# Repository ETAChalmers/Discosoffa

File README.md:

# Discosoffa
Repo för allt vad gäller den fabulösa Discosoffan!

# Index
[Modular BMS](#Modular-BMS)

[MCU-kort](#MCU-kort)

# Modular BMS
Det BMS (Battery Management System) vilket används på soffan är Jonathan Locks egendesignade Modular BMS-projekt. 
PCB-design, kod samt dokumentation för dessa finns att tillgå från hans [GitLab repository](https://gitlab.com/lerneaen_hydra/rabidmantis/tree/master/modular_bms).

Discosoffans batteripack är på 5-celler seriellt (5S). För detta behövs en modul per cell, varav en är master.

Följande är de konfigurationer Discosoffans BMS-moduler använder. Dessa anges i _config.h_.
```c
/** @brief Voltage which gives 100%-active discharge output [volt]
 * Voltages above this value will also keep the discharge output fully on */
#define VTHRS_DISCH_MAX_V				4.00

/** @brief Voltage which gives 0%-active discharge output [volt]
 * Voltages below this value will also keep the discharge output fully off */
#define VTHRS_DISCH_MIN_V				3.95

/** @brief Threshold voltage for activating the charge-disable output [volt] */
#define VTHRS_CHGDIS_START_V			4.05

/** @brief Threshold voltage for de-activating the charge-disable output [volt] */
#define VTHRS_CHGDIS_STOP_V				4.00

/** @brief Threshold voltage for triggering an undervoltage alarm [volt]
 * See also TMIN_UV_ALARM_S */
#define VTHRS_UV_ALARM_V				3.50

/** @brief Threshold voltage for triggering an overvoltage alarm [volt] */
#define VTHRS_OV_ALARM_V				4.10

/** @brief Voltage hysteresis for leaving alarm state [volt]
 * To leave the undervoltage alarm the sampled voltage must exceed
 * VTHRS_UV_ALARM_V + VHYST_ALARMS_V, and to leave the overvoltage
 * alarm the sampled voltage must be below
 * VTHRS_OV_ALARM_V - VHYST_ALARMS_V */
#define VHYST_ALARMS_V					0.05

/** @brief Minimum time the charger will be kept disabled after voltage exceeds
* VTHRS_CHGDIS_START_mv [seconds] */
#define TMIN_CHGDIS_S					30.0

/** @brief Minimum time voltage must be below VTHRS_UV_ALARM_V to trigger an
 * alarm [seconds] */
#define TMIN_UV_ALARM_S					60.0
```

BMS-modulerna är monterade i 3D-printade hållare. 3D STEP-filerna till dessa finns i [bms_box](/mechanics/bms_box). Dessa ser ut som nedan:

# MCU-kort
Kortet vilket sköter styrningen av soffan. Denna huserar en Nucleo-F401RE dev board.

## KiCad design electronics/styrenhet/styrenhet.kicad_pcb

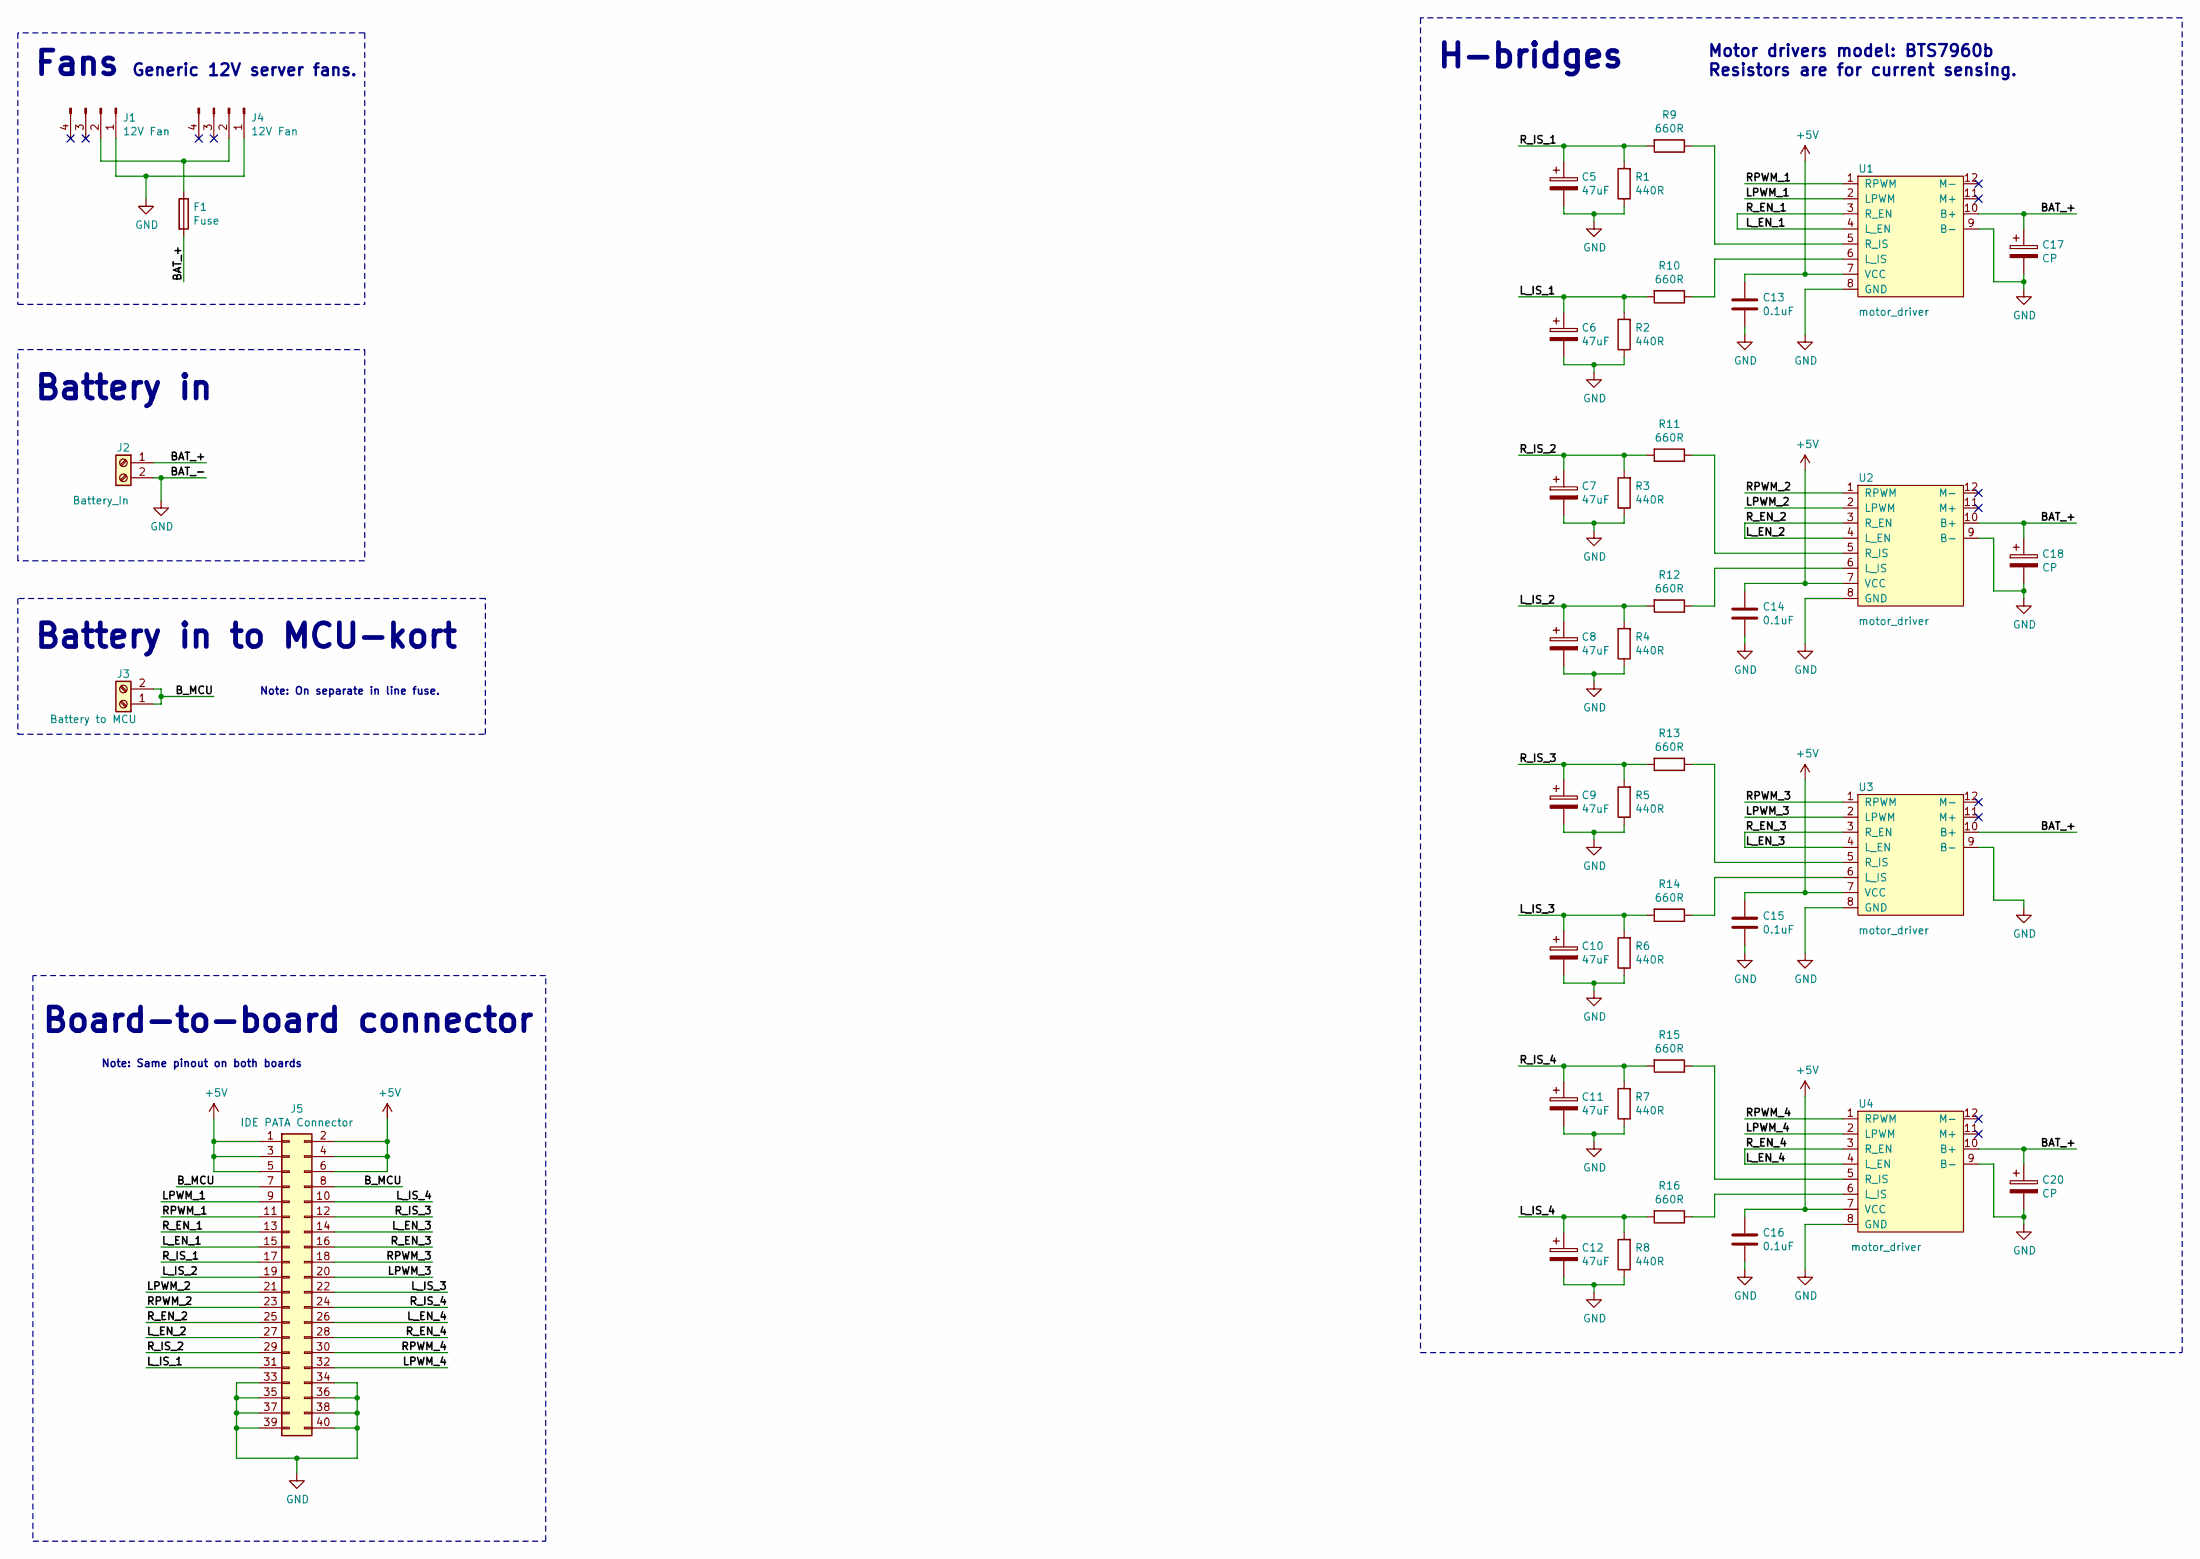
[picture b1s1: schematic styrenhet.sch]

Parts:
C5, C6, C7, C8, C9, C10, C11, C12: 47uF; CP_Radial_D10.0mm_P5.00mm
C13, C14, C15, C16: 0.1uF; C_0805_HandSoldering
C17, C18, C20: CP; CP_Radial_D22.0mm_P10.00mm_SnapIn
F1: Fuse; ETA_thl_fuseholder
J1, J4: 12V Fan; Pin_Header_Straight_1x04_Pitch2.54mm
J2: Battery_In; TerminalBlock-XXL
J3: Battery to MCU; TerminalBlock_Phoenix_MKDS1.5-2pol
J5: IDE PATA Connector; IDC-Header_2x20_Pitch2.54mm_Straight
R1, R2, R3, R4, R5, R6, R7, R8: 440R; R_0603_HandSoldering
R9, R10, R11, R12, R13, R14, R15, R16: 660R; R_0603_HandSoldering
U1, U2, U3, U4: motor_driver; motor-driver

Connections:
+5V: C13.1, C14.1, C15.1, C16.1, J5.1, J5.2, J5.3, J5.4, J5.5, J5.6, U1.7 (VCC), U2.7 (VCC), U3.7 (VCC), U4.7 (VCC)
/BAT_+: C17.1, C18.1, C20.1, F1.2, J2.1, U1.10 (B+), U2.10 (B+), U3.10 (B+), U4.10 (B+)
/B_MCU: J3.1, J3.2, J5.7, J5.8
/LPWM_1: J5.9, U1.2 (LPWM)
/LPWM_2: J5.21, U2.2 (LPWM)
/LPWM_3: J5.20, U3.2 (LPWM)
/LPWM_4: J5.32, U4.2 (LPWM)
/L_EN_1: J5.13, J5.15, U1.3 (R_EN), U1.4 (L_EN)
/L_EN_2: J5.25, J5.27, U2.3 (R_EN), U2.4 (L_EN)
/L_EN_3: J5.14, J5.16, U3.3 (R_EN), U3.4 (L_EN)
/L_EN_4: J5.26, J5.28, U4.3 (R_EN), U4.4 (L_EN)
/L_IS_1: C6.1, J5.31, R2.2, R10.2
/L_IS_2: C8.1, J5.19, R4.2, R12.2
/L_IS_3: C10.1, J5.22, R6.2, R14.2
/L_IS_4: C12.1, J5.10, R8.2, R16.2
/RPWM_1: J5.11, U1.1 (RPWM)
/RPWM_2: J5.23, U2.1 (RPWM)
/RPWM_3: J5.18, U3.1 (RPWM)
/RPWM_4: J5.30, U4.1 (RPWM)
/R_IS_1: C5.1, J5.17, R1.2, R9.2
/R_IS_2: C7.1, J5.29, R3.2, R11.2
/R_IS_3: C9.1, J5.12, R5.2, R13.2
/R_IS_4: C11.1, J5.24, R7.2, R15.2
GND: C5.2, C6.2, C7.2, C8.2, C9.2, C10.2, C11.2, C12.2, C13.2, C14.2, C15.2, C16.2, C17.2, C18.2, C20.2, J1.1, J2.2, J4.1, J5.33, J5.34, J5.35, J5.36, J5.37, J5.38, J5.39, J5.40, R1.1, R2.1, R3.1, R4.1, R5.1, R6.1, R7.1, R8.1, U1.8 (GND), U1.9 (B-), U2.8 (GND), U2.9 (B-), U3.8 (GND), U3.9 (B-), U4.8 (GND), U4.9 (B-)
unnamed: F1.1, J1.2, J4.2
unnamed: R9.1, U1.5 (R_IS)
unnamed: R10.1, U1.6 (L_IS)
unnamed: R11.1, U2.5 (R_IS)
unnamed: R12.1, U2.6 (L_IS)
unnamed: R13.1, U3.5 (R_IS)
unnamed: R14.1, U3.6 (L_IS)
unnamed: R15.1, U4.5 (R_IS)
unnamed: R16.1, U4.6 (L_IS)

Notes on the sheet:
Note: Same pinout on both boards
H-bridges
Motor drivers model: BTS7960b Resistors are for current sensing.
Board-to-board connector
Fans
Generic 12V server fans.
Battery in
Battery in to MCU-kort
Note: On separate in line fuse.

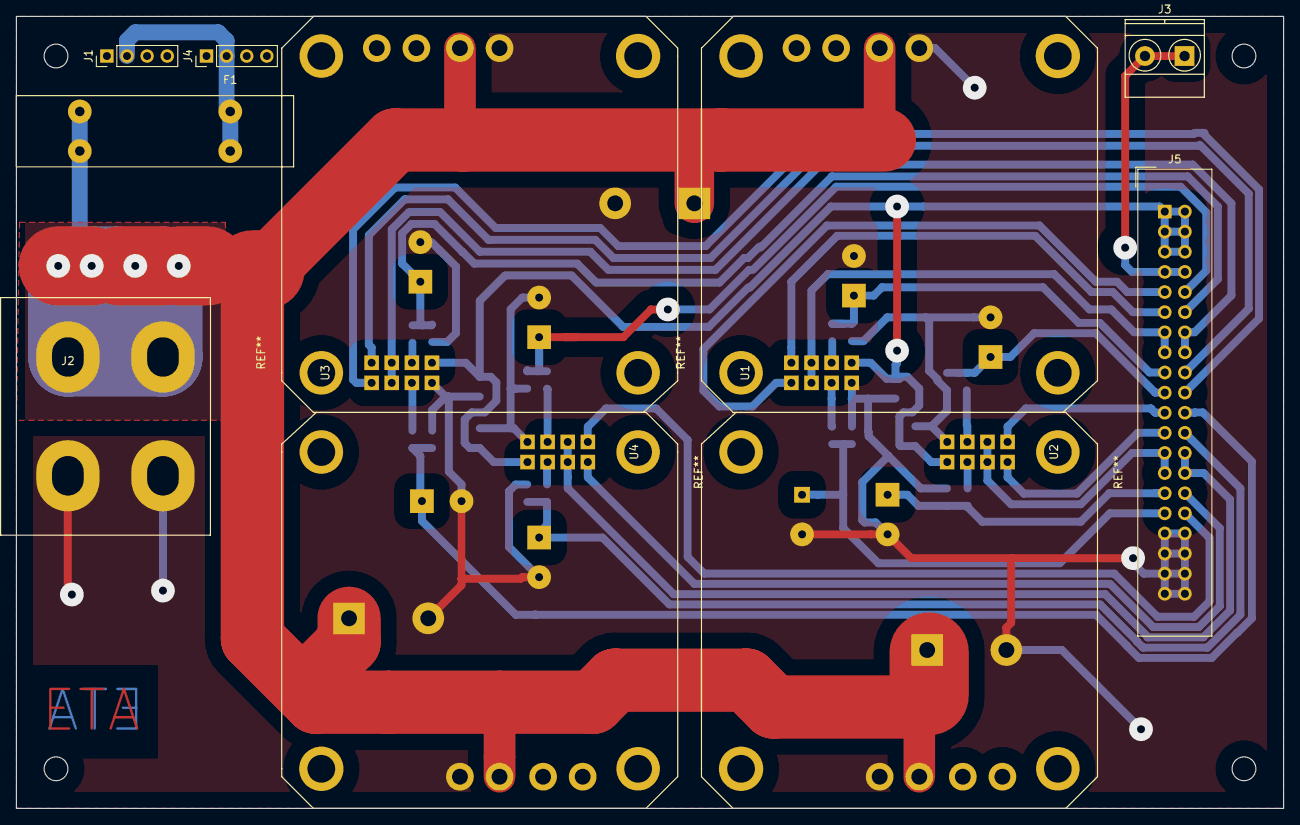
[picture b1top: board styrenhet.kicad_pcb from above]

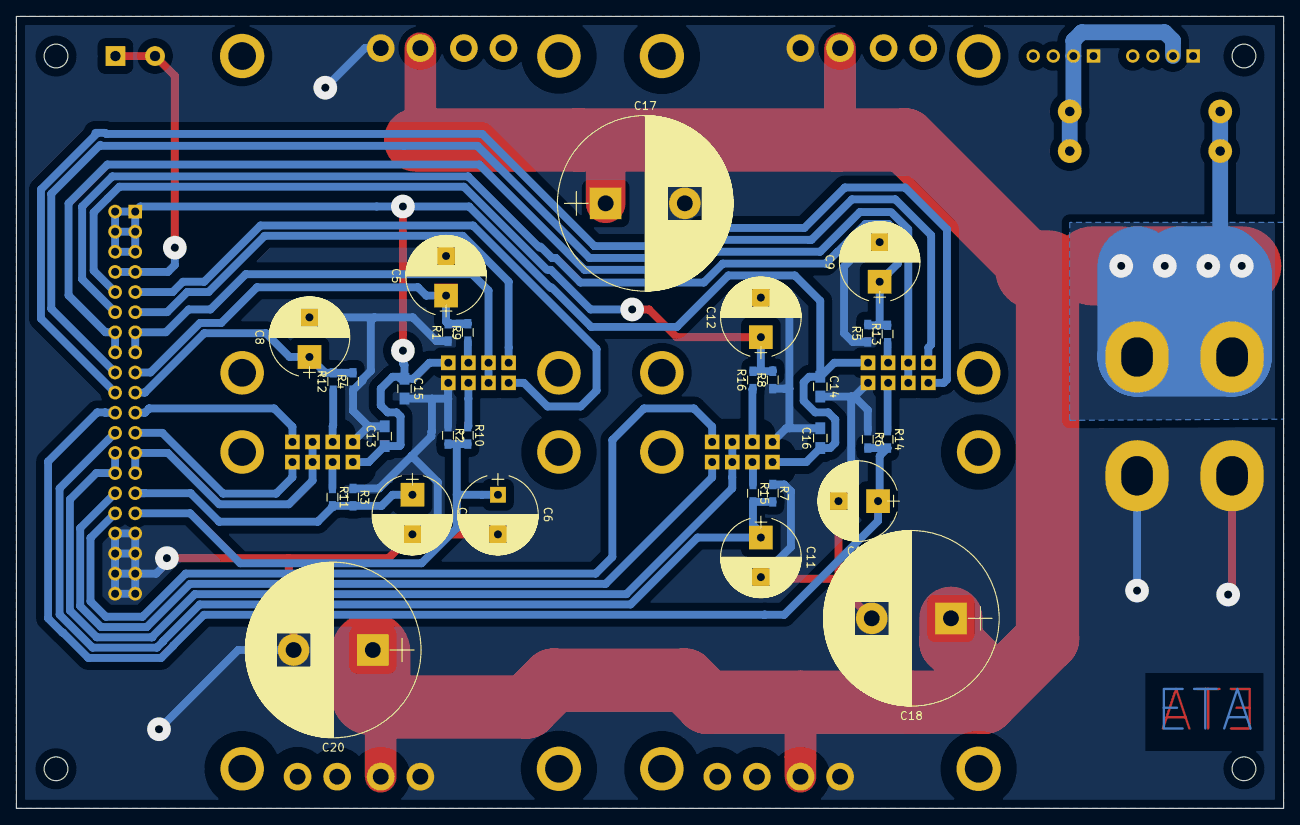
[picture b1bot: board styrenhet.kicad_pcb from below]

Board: 2 copper layers, 160.0 x 100.0 mm, 41 parts (31 on the bottom side), 33 nets.

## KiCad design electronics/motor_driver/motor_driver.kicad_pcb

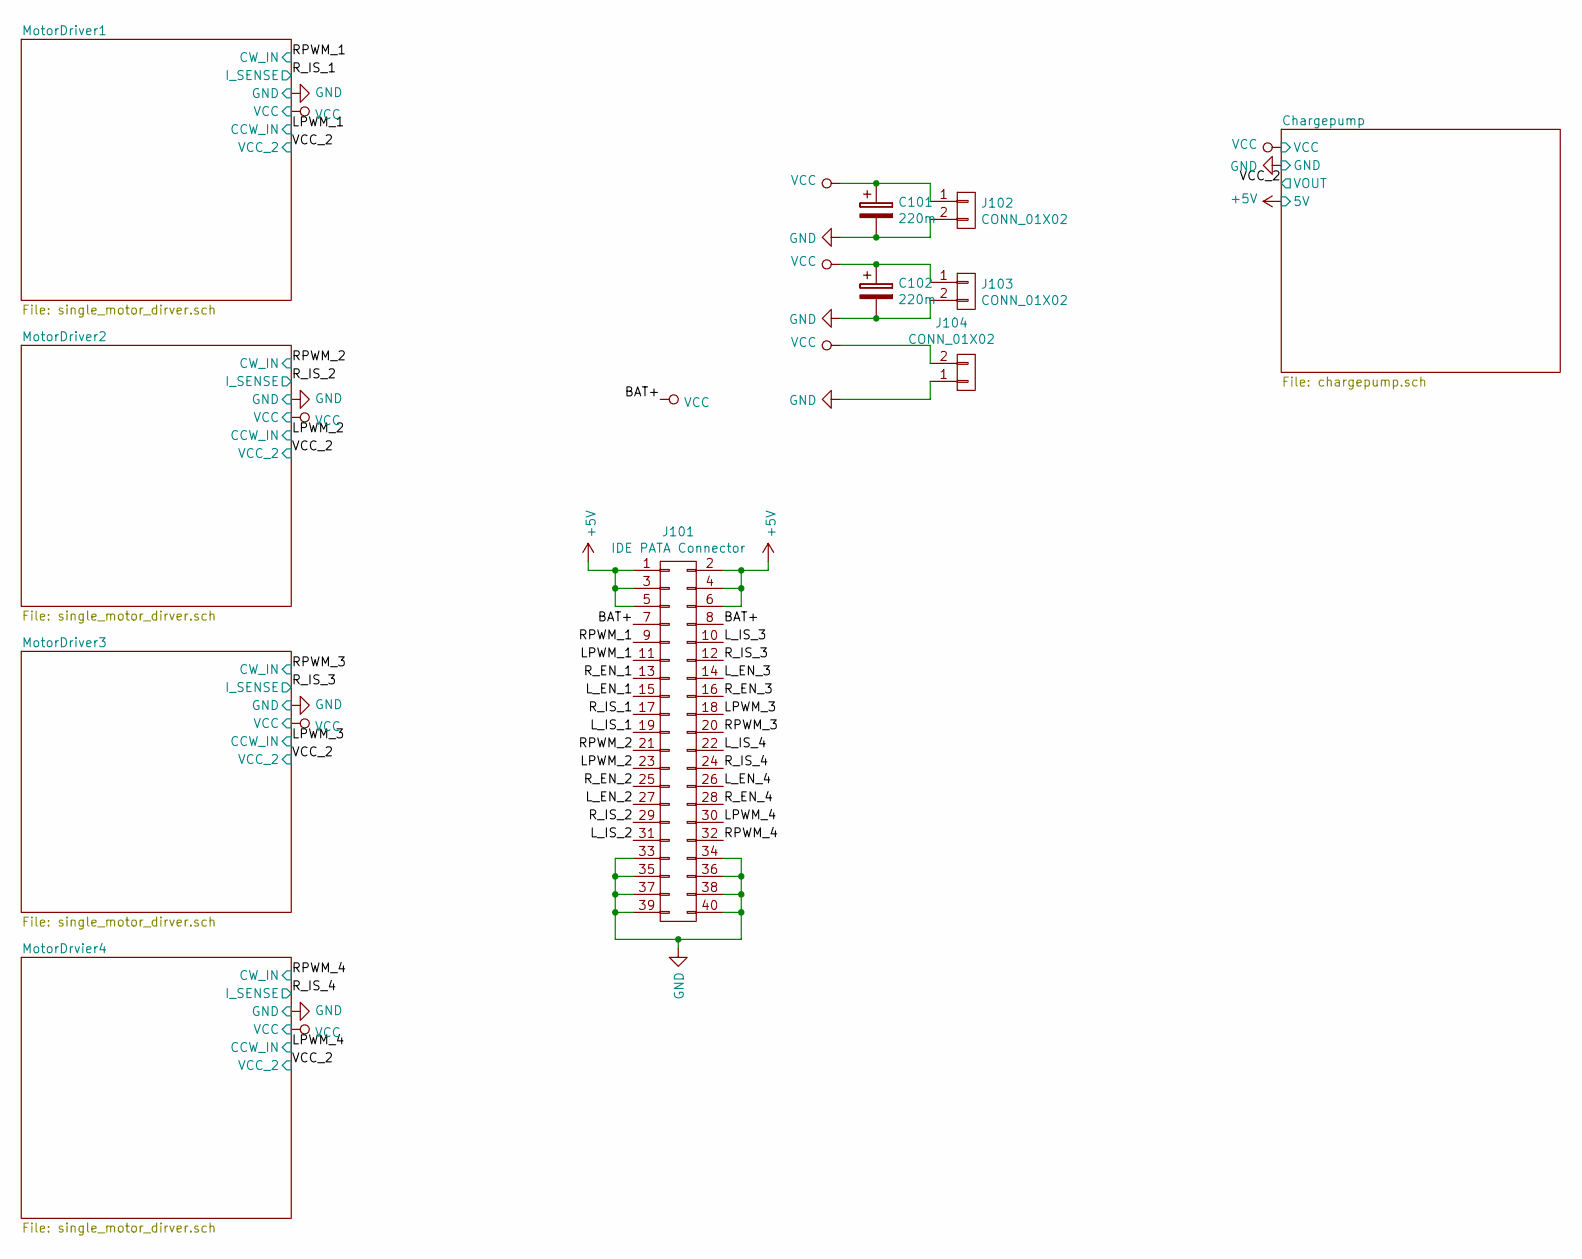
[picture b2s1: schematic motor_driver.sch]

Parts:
C101, C102: 220m; CP_Radial_D25.0mm_P10.00mm_SnapIn
J101: IDE PATA Connector; IDC-Header_2x20_Pitch2.54mm_Straight
J102, J103, J104: CONN_01X02; TerminalBlock-XXL

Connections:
+5V: J101.1, J101.2, J101.3, J101.4, J101.5, J101.6; also elsewhere on the board
/LPWM_1: J101.11; also elsewhere on the board
/LPWM_2: J101.23; also elsewhere on the board
/LPWM_3: J101.18; also elsewhere on the board
/LPWM_4: J101.30; also elsewhere on the board
/L_EN_1: J101.15
/L_EN_2: J101.27
/L_EN_3: J101.14
/L_EN_4: J101.26
/L_IS_1: J101.19
/L_IS_2: J101.31
/L_IS_3: J101.10
/L_IS_4: J101.22
/RPWM_1: J101.9; also elsewhere on the board
/RPWM_2: J101.21; also elsewhere on the board
/RPWM_3: J101.20; also elsewhere on the board
/RPWM_4: J101.32; also elsewhere on the board
/R_EN_1: J101.13
/R_EN_2: J101.25
/R_EN_3: J101.16
/R_EN_4: J101.28
/R_IS_1: J101.17; also elsewhere on the board
/R_IS_2: J101.29; also elsewhere on the board
/R_IS_3: J101.12; also elsewhere on the board
/R_IS_4: J101.24; also elsewhere on the board
GND: C101.2, C102.2, J101.33, J101.34, J101.35, J101.36, J101.37, J101.38, J101.39, J101.40, J102.2, J103.2, J104.1; also elsewhere on the board
VCC: C101.1, C102.1, J101.7, J101.8, J102.1, J103.1, J104.2; also elsewhere on the board

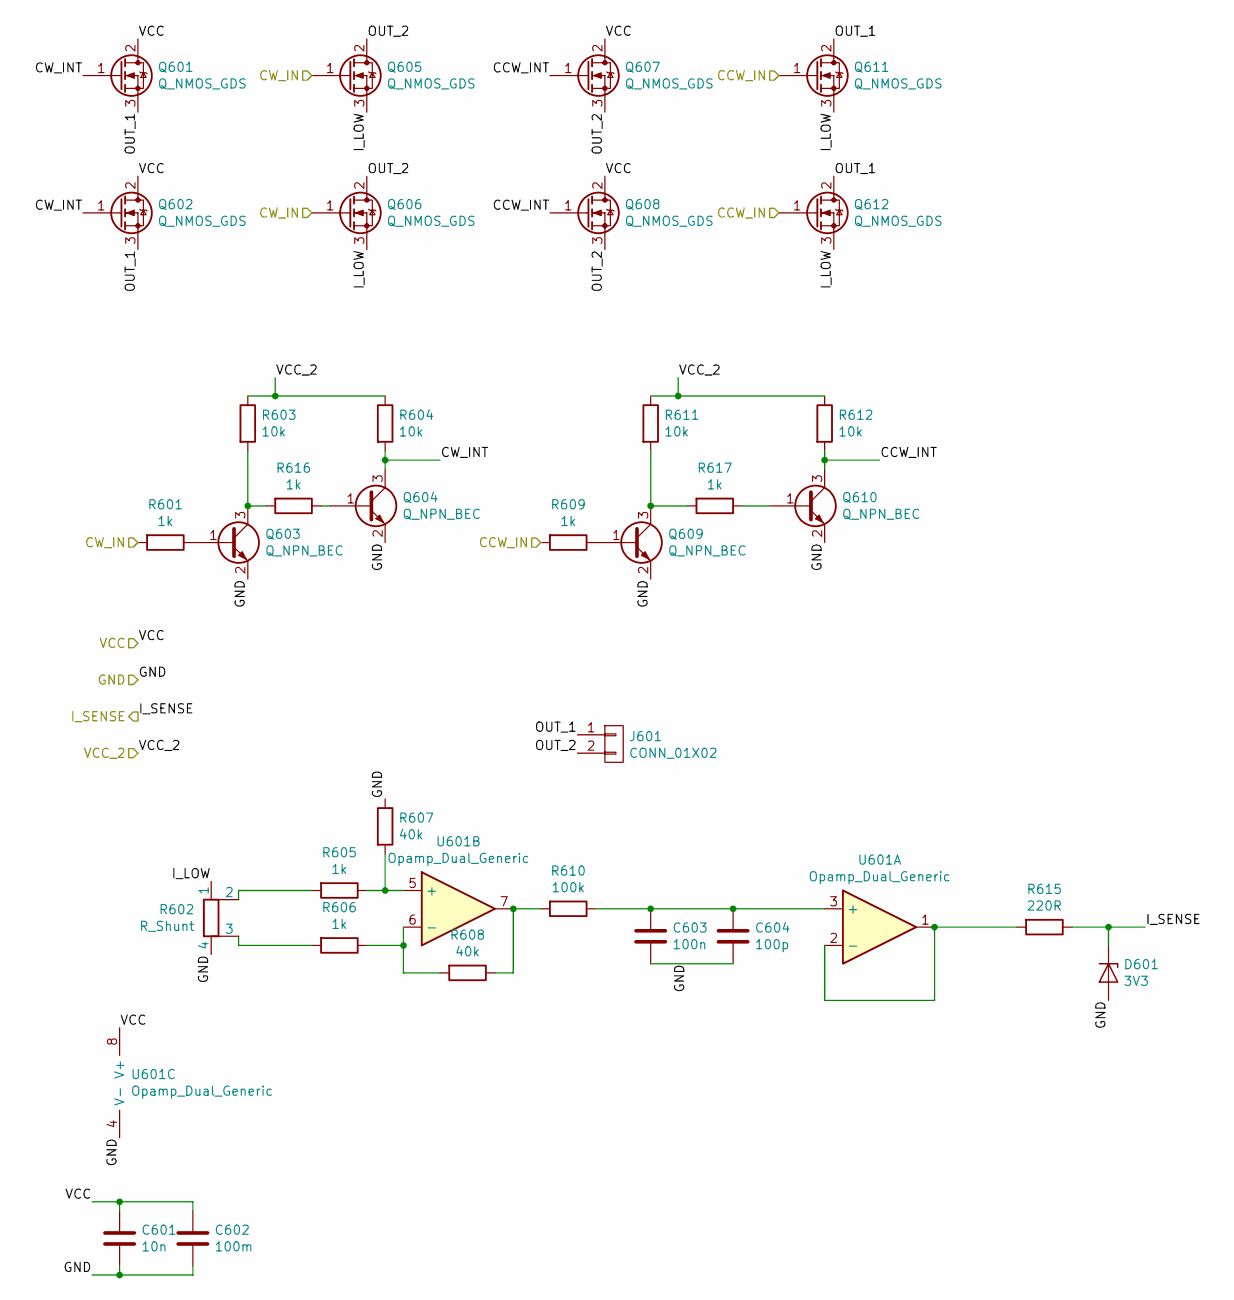
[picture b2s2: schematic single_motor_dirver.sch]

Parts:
C201: 10n; C_0805_HandSoldering
C202: 100m; CP_Radial_D8.0mm_P3.50mm
C203: 100n; C_0805_HandSoldering
C204: 100p; C_0805_HandSoldering
D201: 3V3; D_DO-35_SOD27_P5.08mm_Vertical_AnodeUp
J201: CONN_01X02; AK300-2
Q201, Q202, Q205, Q206, Q207, Q208, Q211, Q212: Q_NMOS_GDS; TO-220-3_Horizontal_Reversed
Q203, Q204, Q209, Q210: Q_NPN_BEC; SOT-23
R201, R205, R206, R209, R216, R217: 1k; R_0805_HandSoldering
R203, R204, R211, R212: 10k; R_0805_HandSoldering
R207, R208: 40k; R_0805_HandSoldering
R210: 100k; R_0805_HandSoldering
R215: 220R; R_0805_HandSoldering
R602: R_Shunt; 10uOhmShunt
U201: Opamp_Dual_Generic; SOIC-8-N

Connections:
/LPWM_1: Q211.1 (G), Q212.1 (G), R209.2; also elsewhere on the board
/MotorDriver1/CCW_INT: Q207.1 (G), Q208.1 (G), Q210.3 (C), R212.2
/MotorDriver1/CW_INT: Q201.1 (G), Q202.1 (G), Q204.3 (C), R204.2
/MotorDriver1/OUT_1: J201.1, Q201.3 (S), Q202.3 (S), Q211.2 (D), Q212.2 (D)
/MotorDriver1/OUT_2: J201.2, Q205.2 (D), Q206.2 (D), Q207.3 (S), Q208.3 (S)
/RPWM_1: Q205.1 (G), Q206.1 (G), R201.2; also elsewhere on the board
/R_IS_1: D201.1 (K), R215.1; also elsewhere on the board
/VCC_2: R203.1, R204.1, R211.1, R212.1; also elsewhere on the board
GND: C201.2, C202.2, C203.2, C204.2, D201.2 (A), Q203.2 (E), Q204.2 (E), Q209.2 (E), Q210.2 (E), R207.1, R602.4, U201.4 (V-); also elsewhere on the board
unnamed: C203.1, C204.1, R210.1, U201.3 (+)
unnamed: Q203.1 (B), R201.1
unnamed: Q203.3 (C), R203.2, R216.2
unnamed: Q204.1 (B), R216.1
unnamed: Q209.1 (B), R209.1
unnamed: Q209.3 (C), R211.2, R217.2
unnamed: Q210.1 (B), R217.1
unnamed: R205.1, R207.2, U201.5 (+)
unnamed: R206.1, R208.2, U201.6 (-)
unnamed: R208.1, R210.2, U201.7
unnamed: R215.2, U201.1, U201.2 (-)
VCC: C201.1, C202.1, Q201.2 (D), Q202.2 (D), Q207.2 (D), Q208.2 (D), U201.8 (V+); also elsewhere on the board

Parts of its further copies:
C401, C501, C601: 10n; C_0805_HandSoldering
C402, C502, C602: 100m; CP_Radial_D8.0mm_P3.50mm
C403, C503, C603: 100n; C_0805_HandSoldering
C404, C504, C604: 100p; C_0805_HandSoldering
D401, D501, D601: 3V3; D_DO-35_SOD27_P5.08mm_Vertical_AnodeUp
J401, J501, J601: CONN_01X02; AK300-2
Q401, Q402, Q405, Q406, Q407, Q408, Q411, Q412, Q501, Q502, Q505, Q506, Q507, Q508, Q511, Q512, Q601, Q602, Q605, Q606, Q607, Q608, Q611, Q612: Q_NMOS_GDS; TO-220-3_Horizontal_Reversed
Q403, Q404, Q409, Q410, Q503, Q504, Q509, Q510, Q603, Q604, Q609, Q610: Q_NPN_BEC; SOT-23
R202, R402, R502: R_Shunt; 10uOhmShunt
R401, R405, R406, R409, R416, R417, R501, R505, R506, R509, R516, R517, R601, R605, R606, R609, R616, R617: 1k; R_0805_HandSoldering
R403, R404, R411, R412, R503, R504, R511, R512, R603, R604, R611, R612: 10k; R_0805_HandSoldering
R407, R408, R507, R508, R607, R608: 40k; R_0805_HandSoldering
R410, R510, R610: 100k; R_0805_HandSoldering
R415, R515, R615: 220R; R_0805_HandSoldering
U401, U501, U601: Opamp_Dual_Generic; SOIC-8-N

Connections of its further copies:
/LPWM_2: Q411.1 (G), Q412.1 (G), R409.2; also elsewhere on the board
/LPWM_3: Q511.1 (G), Q512.1 (G), R509.2; also elsewhere on the board
/LPWM_4: Q611.1 (G), Q612.1 (G), R609.2; also elsewhere on the board
/MotorDriver2/CCW_INT: Q407.1 (G), Q408.1 (G), Q410.3 (C), R412.2
/MotorDriver2/CW_INT: Q401.1 (G), Q402.1 (G), Q404.3 (C), R404.2
/MotorDriver2/I_LOW: Q405.3 (S), Q406.3 (S), Q411.3 (S), Q412.3 (S), R402.1
/MotorDriver2/OUT_1: J401.1, Q401.3 (S), Q402.3 (S), Q411.2 (D), Q412.2 (D)
/MotorDriver2/OUT_2: J401.2, Q405.2 (D), Q406.2 (D), Q407.3 (S), Q408.3 (S)
/MotorDriver3/CCW_INT: Q507.1 (G), Q508.1 (G), Q510.3 (C), R512.2
/MotorDriver3/CW_INT: Q501.1 (G), Q502.1 (G), Q504.3 (C), R504.2
/MotorDriver3/I_LOW: Q505.3 (S), Q506.3 (S), Q511.3 (S), Q512.3 (S), R502.1
/MotorDriver3/OUT_1: J501.1, Q501.3 (S), Q502.3 (S), Q511.2 (D), Q512.2 (D)
/MotorDriver3/OUT_2: J501.2, Q505.2 (D), Q506.2 (D), Q507.3 (S), Q508.3 (S)
/MotorDrvier4/CCW_INT: Q607.1 (G), Q608.1 (G), Q610.3 (C), R612.2
/MotorDrvier4/CW_INT: Q601.1 (G), Q602.1 (G), Q604.3 (C), R604.2
/MotorDrvier4/OUT_1: J601.1, Q601.3 (S), Q602.3 (S), Q611.2 (D), Q612.2 (D)
/MotorDrvier4/OUT_2: J601.2, Q605.2 (D), Q606.2 (D), Q607.3 (S), Q608.3 (S)
/RPWM_2: Q405.1 (G), Q406.1 (G), R401.2; also elsewhere on the board
/RPWM_3: Q505.1 (G), Q506.1 (G), R501.2; also elsewhere on the board
/RPWM_4: Q605.1 (G), Q606.1 (G), R601.2; also elsewhere on the board
/R_IS_2: D401.1 (K), R415.1; also elsewhere on the board
/R_IS_3: D501.1 (K), R515.1; also elsewhere on the board
/R_IS_4: D601.1 (K), R615.1; also elsewhere on the board
/VCC_2: R403.1, R404.1, R411.1, R412.1, R503.1, R504.1, R511.1, R512.1, R603.1, R604.1, R611.1, R612.1; also elsewhere on the board
GND: C401.2, C402.2, C403.2, C404.2, C501.2, C502.2, C503.2, C504.2, C601.2, C602.2, C603.2, C604.2, D401.2 (A), D501.2 (A), D601.2 (A), Q403.2 (E), Q404.2 (E), Q409.2 (E), Q410.2 (E), Q503.2 (E), Q504.2 (E), Q509.2 (E), Q510.2 (E), Q603.2 (E), Q604.2 (E), Q609.2 (E), Q610.2 (E), R202.4, R402.4, R407.1, R502.4, R507.1, R607.1, U401.4 (V-), U501.4 (V-), U601.4 (V-); also elsewhere on the board
unnamed: C403.1, C404.1, R410.1, U401.3 (+)
unnamed: C503.1, C504.1, R510.1, U501.3 (+)
unnamed: C603.1, C604.1, R610.1, U601.3 (+)
unnamed: Q403.1 (B), R401.1
unnamed: Q403.3 (C), R403.2, R416.2
unnamed: Q404.1 (B), R416.1
unnamed: Q409.1 (B), R409.1
unnamed: Q409.3 (C), R411.2, R417.2
unnamed: Q410.1 (B), R417.1
unnamed: Q503.1 (B), R501.1
unnamed: Q503.3 (C), R503.2, R516.2
unnamed: Q504.1 (B), R516.1
unnamed: Q509.1 (B), R509.1
unnamed: Q509.3 (C), R511.2, R517.2
unnamed: Q510.1 (B), R517.1
unnamed: Q603.1 (B), R601.1
unnamed: Q603.3 (C), R603.2, R616.2
unnamed: Q604.1 (B), R616.1
unnamed: Q609.1 (B), R609.1
unnamed: Q609.3 (C), R611.2, R617.2
unnamed: Q610.1 (B), R617.1
unnamed: R402.2, R405.2
unnamed: R402.3, R406.2
unnamed: R405.1, R407.2, U401.5 (+)
unnamed: R406.1, R408.2, U401.6 (-)
unnamed: R408.1, R410.2, U401.7
unnamed: R415.2, U401.1, U401.2 (-)
unnamed: R502.2, R505.2
unnamed: R502.3, R506.2
unnamed: R505.1, R507.2, U501.5 (+)
unnamed: R506.1, R508.2, U501.6 (-)
unnamed: R508.1, R510.2, U501.7
unnamed: R515.2, U501.1, U501.2 (-)
unnamed: R605.1, R607.2, U601.5 (+)
unnamed: R606.1, R608.2, U601.6 (-)
unnamed: R608.1, R610.2, U601.7
unnamed: R615.2, U601.1, U601.2 (-)
VCC: C401.1, C402.1, C501.1, C502.1, C601.1, C602.1, Q401.2 (D), Q402.2 (D), Q407.2 (D), Q408.2 (D), Q501.2 (D), Q502.2 (D), Q507.2 (D), Q508.2 (D), Q601.2 (D), Q602.2 (D), Q607.2 (D), Q608.2 (D), U401.8 (V+), U501.8 (V+), U601.8 (V+); also elsewhere on the board

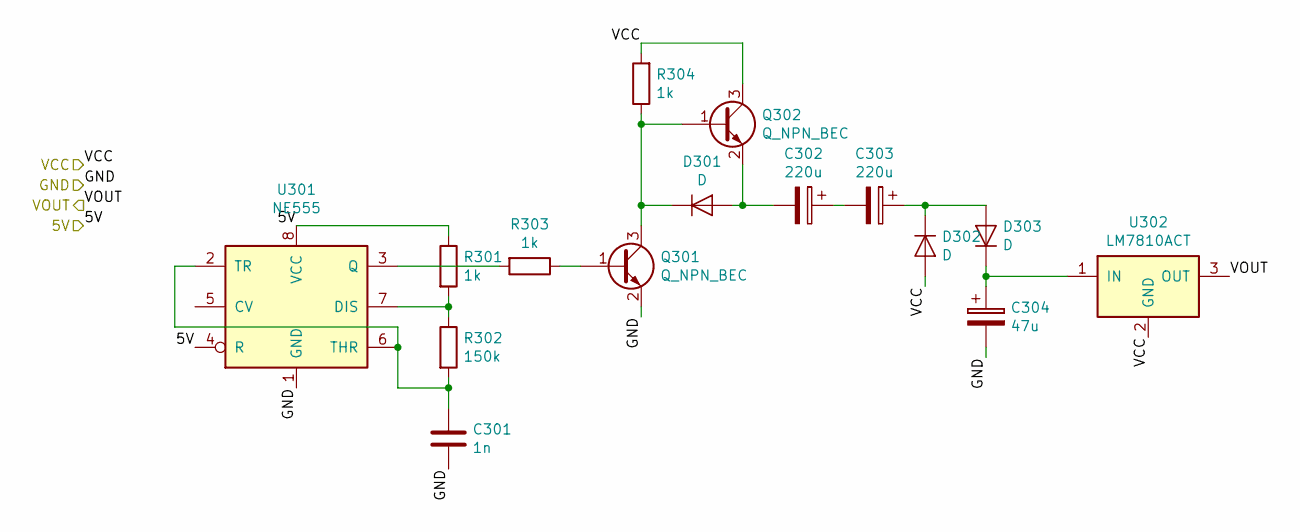
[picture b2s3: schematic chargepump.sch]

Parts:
C301: 1n; C_0805_HandSoldering
C302, C303: 220u; CP_Radial_D5.0mm_P2.50mm
C304: 47u; CP_Radial_D5.0mm_P2.50mm
D301, D302, D303: D; D_T-1_P5.08mm_Horizontal
Q301, Q302: Q_NPN_BEC; SOT-23_Handsoldering
R301, R303, R304: 1k; R_0805_HandSoldering
R302: 150k; R_0805_HandSoldering
U301: NE555; SOIC-8-N
U302: LM7810ACT; TO-220_Horizontal

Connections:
+5V: R301.1, U301.4 (R), U301.8 (VCC); also elsewhere on the board
/VCC_2: U302.3 (OUT); also elsewhere on the board
GND: C301.2, C304.2, Q301.2 (E), U301.1 (GND); also elsewhere on the board
unnamed: C301.1, R302.2, U301.2 (TR), U301.6 (THR)
unnamed: C302.1, C303.2
unnamed: C302.2, D301.2 (A), Q302.2 (E)
unnamed: C303.1, D302.1 (K), D303.2 (A)
unnamed: C304.1, D303.1 (K), U302.1 (IN)
unnamed: D301.1 (K), Q301.3 (C), Q302.1 (B), R304.1
unnamed: Q301.1 (B), R303.1
unnamed: R301.2, R302.1, U301.7 (DIS)
unnamed: R303.2, U301.3 (Q)
VCC: D302.2 (A), Q302.3 (C), R304.2, U302.2 (GND); also elsewhere on the board

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
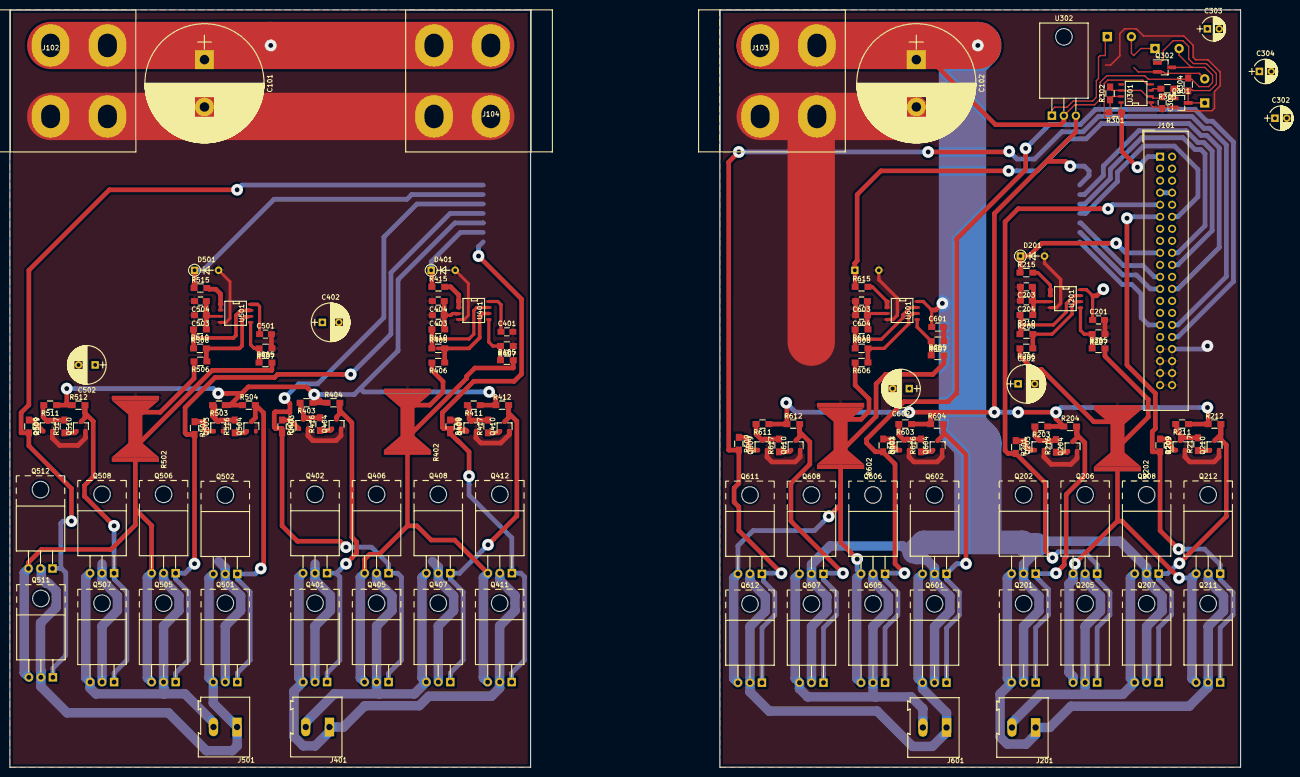
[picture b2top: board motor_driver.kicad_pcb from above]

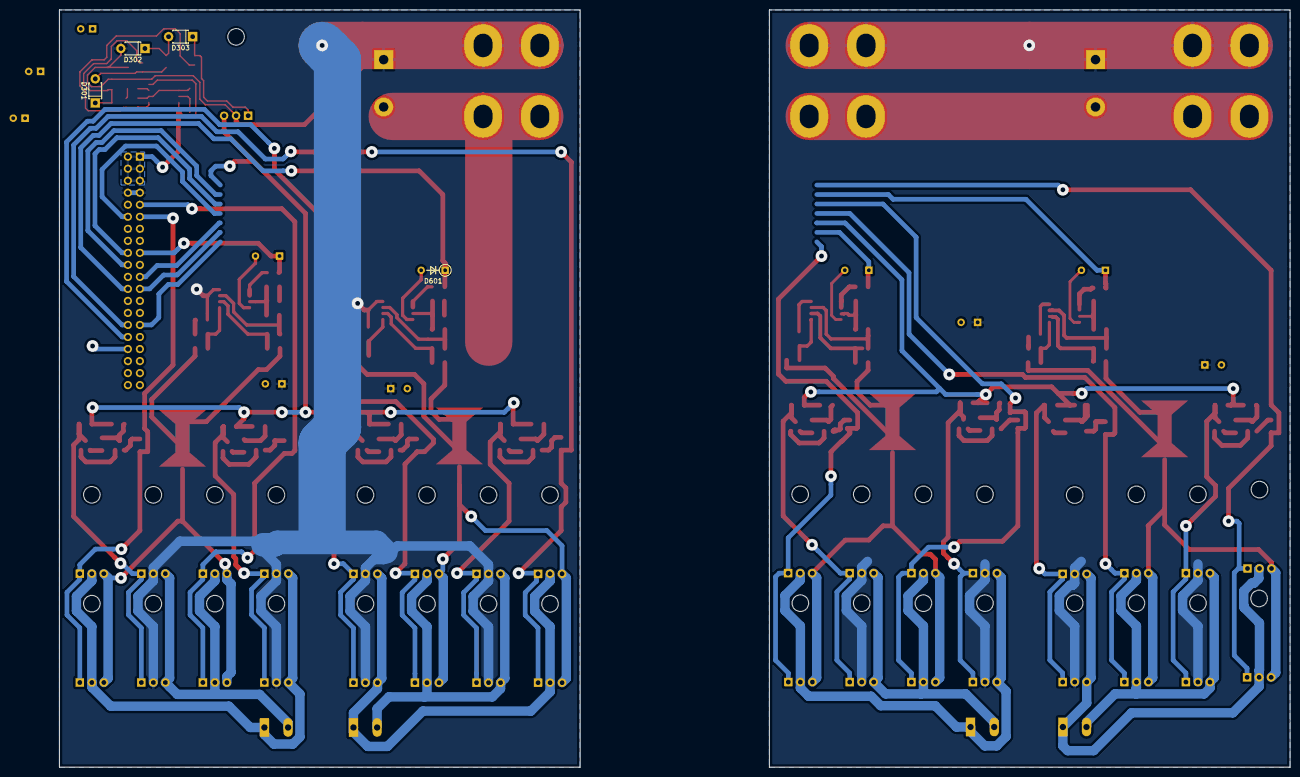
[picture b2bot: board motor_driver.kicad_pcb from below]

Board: 2 copper layers, 260.0 x 160.0 mm, 157 parts (4 on the bottom side), 97 nets.

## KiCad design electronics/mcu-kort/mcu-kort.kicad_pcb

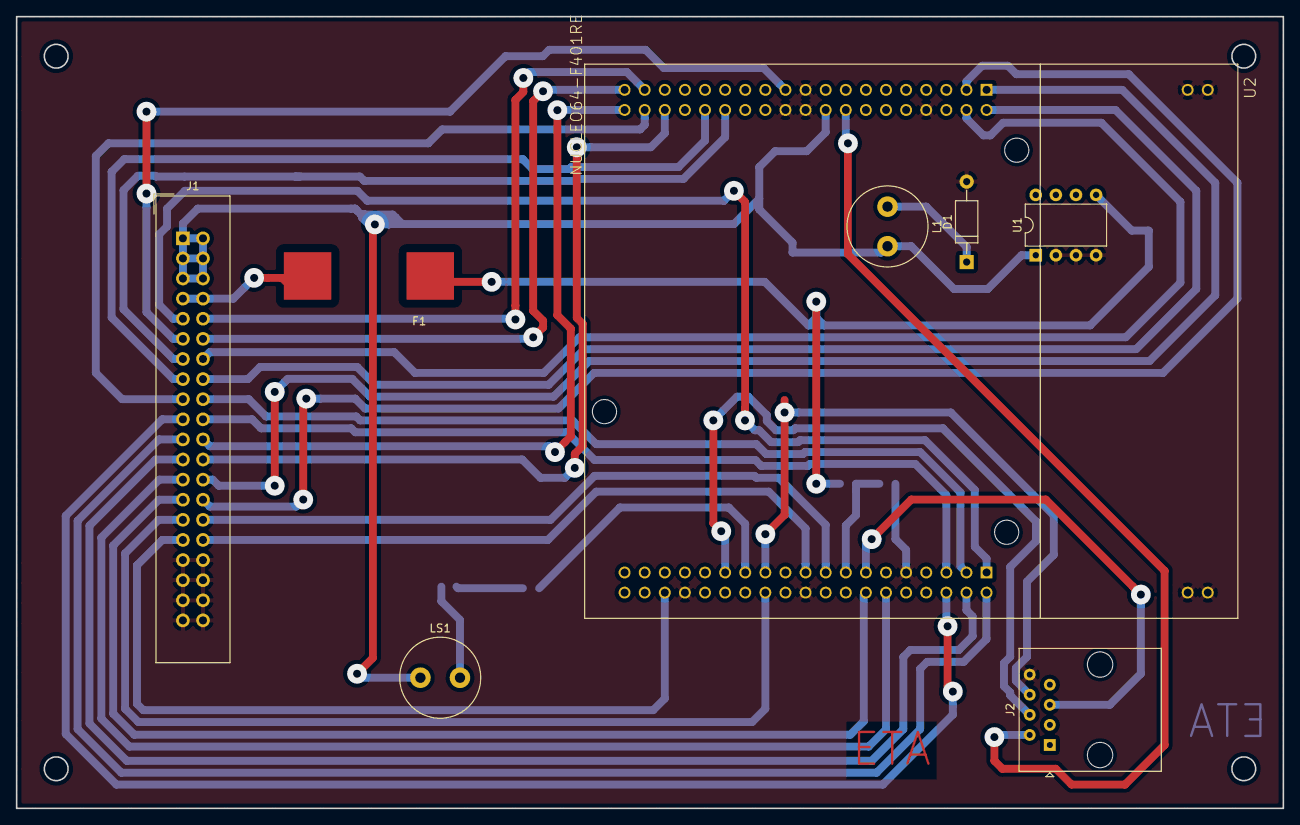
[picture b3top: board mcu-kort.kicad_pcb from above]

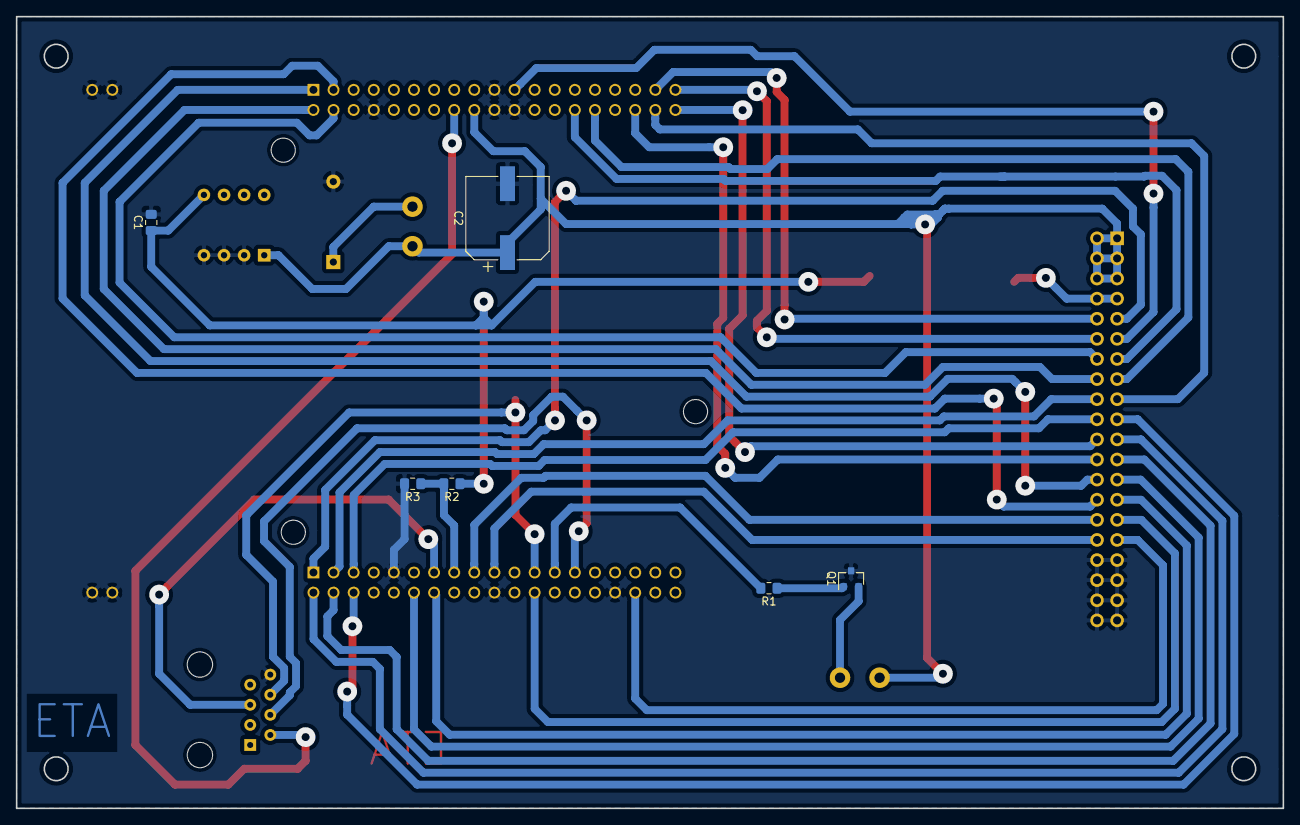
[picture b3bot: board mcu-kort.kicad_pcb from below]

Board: 2 copper layers, 160.0 x 100.0 mm, 14 parts (6 on the bottom side), 37 nets.

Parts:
C1: 22uF; C_0805_2012Metric_Pad1.15x1.40mm_HandSolder
C2: 220uF; CP_Elec_10x7.9
D1: 11DQ06; D_A-405_P10.16mm_Horizontal
F1: 0.5A; SMD_Fuse_holder
J1: IDE PATA Connector; IDC-Header_2x20_P2.54mm_Vertical
J2: RJ45; RJ45_Amphenol_54602-x08_Horizontal
L1: 330uH; L_Radial_D10.0mm_P5.00mm_Fastron_07M
LS1: Piezo; L_Radial_D10.0mm_P5.00mm_Fastron_07M
Q1: Godtycklig; SOT-23
R1: 1k; R_0805_2012Metric_Pad1.15x1.40mm_HandSolder
R2: 56k; R_0805_2012Metric_Pad1.15x1.40mm_HandSolder
R3: 8.2k; R_0805_2012Metric_Pad1.15x1.40mm_HandSolder
U1: LM2574HVN-5; DIP-8_W7.62mm
U2: NUCLEO64-F401RE; MODULE_NUCLEO-F401RE.pretty

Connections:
+3V3: J2.2, U2.16
+5V: C2.1, J1.1, J1.2, J1.3, J1.4, J1.5, J1.6, L1.2, LS1.1, U1.1, U2.18
+BATT: C1.1, F1.1, R2.1, U1.5
/BAT+: F1.2, J1.7, J1.8
/B_Vread: R2.2, R3.1, U2.53
/Device_detect: J2.5, U2.51
/I2C3_SCL: J2.6, U2.61
/I2C3_SDA: J2.4, U2.65
/LPWM_1: J1.11, U2.21
/LPWM_2: J1.23, U2.42
/LPWM_3: J1.18, U2.41
/LPWM_4: J1.30, U2.55
/L_EN_1: J1.15, U2.30
/L_EN_2: J1.27, U2.52
/L_EN_3: J1.14, U2.4
/L_EN_4: J1.26, U2.1
/L_IS_1: J1.19, U2.44
/L_IS_2: J1.31, U2.72
/L_IS_3: J1.10, U2.35
/L_IS_4: J1.22, U2.38
/Piezo: R1.2, U2.63
/RPWM_1: J1.9, U2.39
/RPWM_2: J1.21, U2.40
/RPWM_3: J1.20, U2.43
/RPWM_4: J1.32, U2.57
/R_EN_1: J1.13, U2.28
/R_EN_2: J1.25, U2.50
/R_EN_3: J1.16, U2.2
/R_EN_4: J1.28, U2.3
/R_IS_1: J1.17, U2.36
/R_IS_2: J1.29, U2.62
/R_IS_3: J1.12, U2.37
/R_IS_4: J1.24, U2.34
GND: C1.2, C2.2, D1.2, J1.33, J1.34, J1.35, J1.36, J1.37, J1.38, J1.39, J1.40, J2.8, Q1.3, R3.2, U1.2, U1.3, U1.4, U2.8, U2.19, U2.20, U2.22, U2.47, U2.58, U2.70, U2.77, U2.78, U2.79, U2.80
unnamed: D1.1, L1.1
unnamed: LS1.2, Q1.2
unnamed: Q1.1, R1.1
